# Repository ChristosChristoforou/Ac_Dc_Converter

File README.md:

# Ac_Dc_Converter
High power Ac to Dc Converter

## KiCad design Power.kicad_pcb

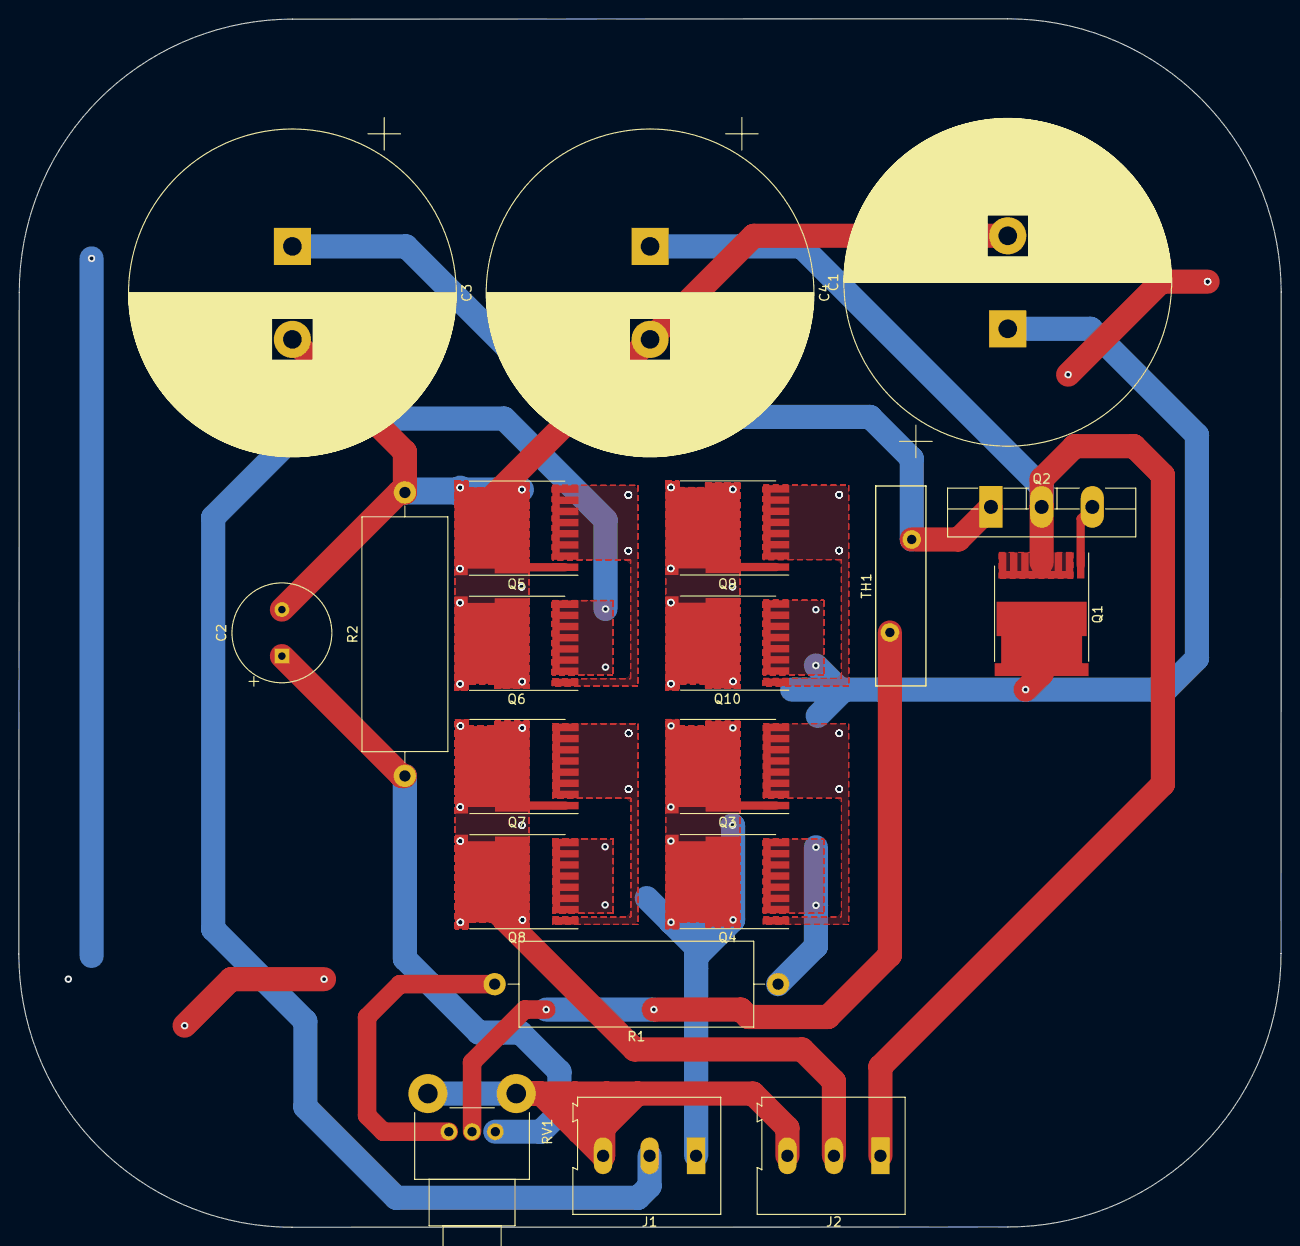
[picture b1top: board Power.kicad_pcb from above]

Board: 2 copper layers, 135.7 x 129.9 mm, 20 parts (0 on the bottom side), 15 nets.

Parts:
C1, C3, C4: 10m/100V; CP_Radial_D35.0mm_P10.00mm_SnapIn
C2: 1u/60V/solid_tantalum; CP_Radial_Tantal_D10.5mm_P5.00mm
J1, J2: Conn_01x03_Female; TerminalBlock_Altech_AK300-3_P5.00mm
Q1, Q3, Q4, Q5, Q6, Q7, Q8, Q9, Q10: IPT015N10N5; Infineon_PG-HSOF-8-1
Q2: BD250C; TO-264-3_Vertical
R1, R2: 50k; R_Axial_Power_L25.0mm_W9.0mm_P30.48mm
RV1: 20k; Potentiometer_Alps_RK09L_Single_Horizontal
TH1: Thermistor_PTC_US_50ohm; RV_Disc_D21.5mm_W5.4mm_P10mm

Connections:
/AC_1: J1.1, Q3.1, Q3.3, Q4.3, Q8.2
/AC_2: J1.2, Q6.2, Q9.1, Q9.3, Q10.3
/Sheet611FEA1C/D-: C1.1, Q1.3, Q4.2, Q10.2, R1.1
/V+: C4.1, J2.1, Q1.2, Q2.2
Earth: C1.2, C2.2, C3.2, C4.2, J2.2, Q5.1, Q5.3, Q6.3, Q7.1, Q7.3, Q8.3, R2.2
GNDPWR: J1.3, J2.3
unnamed: C2.1, R2.1, RV1.3
unnamed: C3.1, Q2.1, TH1.1
unnamed: Q1.1, Q2.3
unnamed: Q3.2, Q4.1
unnamed: Q5.2, Q6.1
unnamed: Q7.2, Q8.1
unnamed: Q9.2, Q10.1
unnamed: R1.2, RV1.1
unnamed: RV1.2, TH1.2
